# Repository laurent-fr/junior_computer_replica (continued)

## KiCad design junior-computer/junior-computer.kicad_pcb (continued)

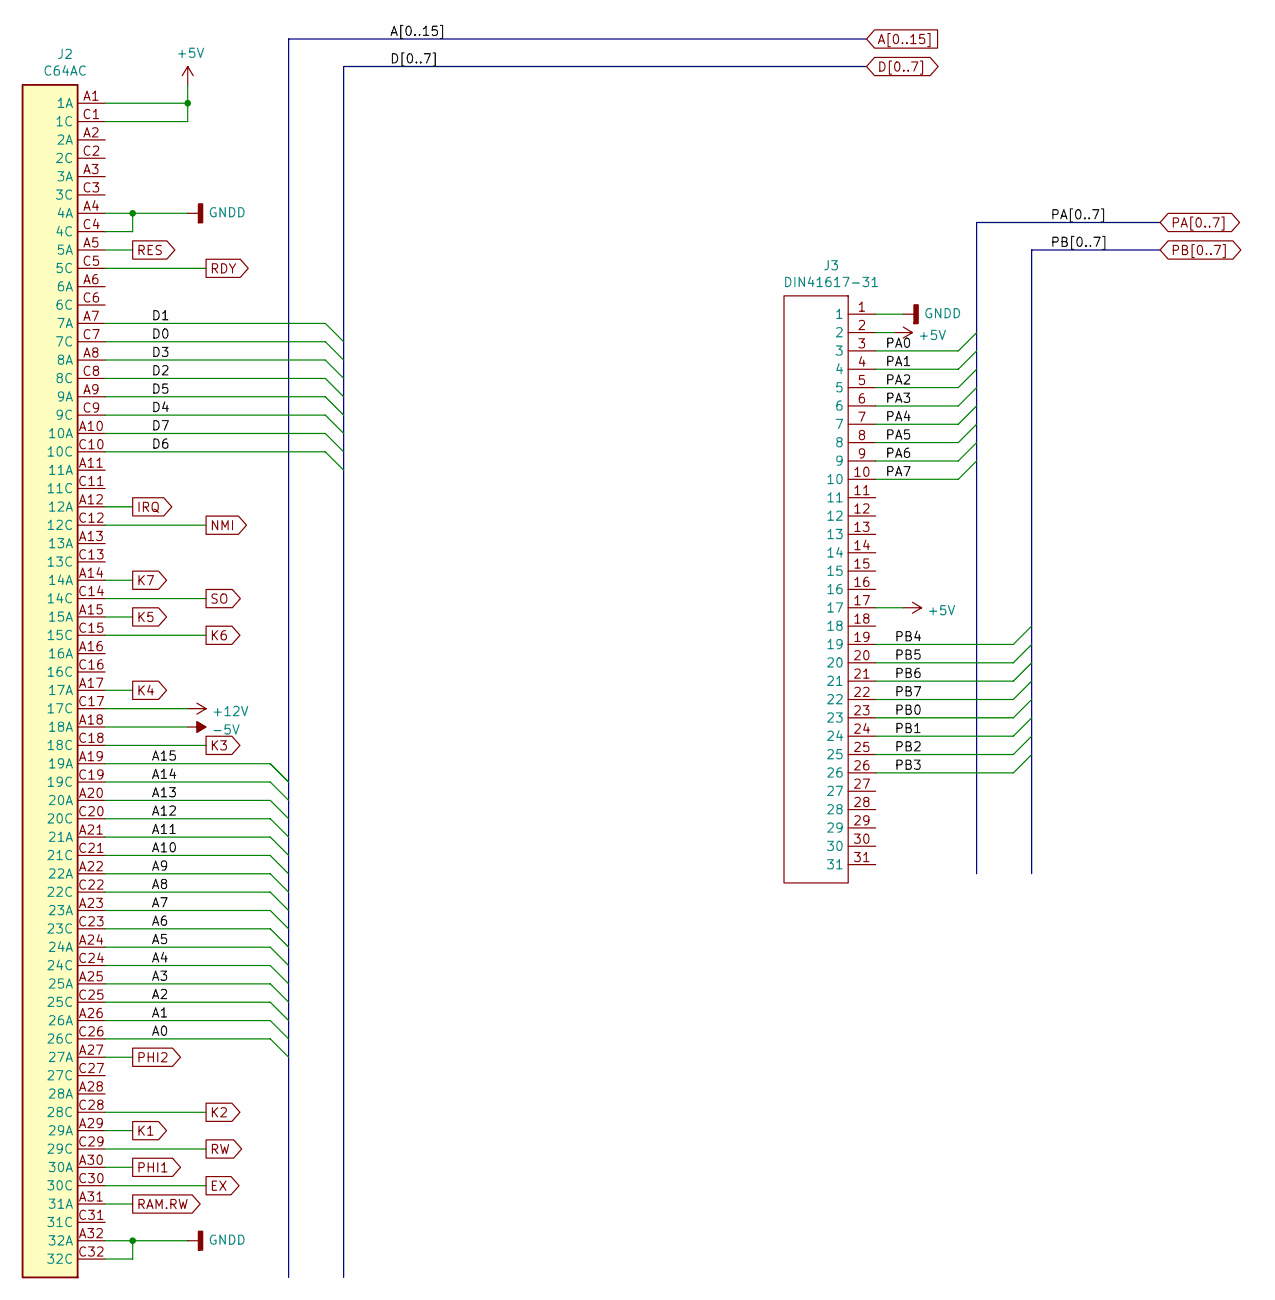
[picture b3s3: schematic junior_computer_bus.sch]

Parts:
J2: C64AC; DIN-41612-AC
J3: DIN41617-31; DIN-41617-31-F

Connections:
+5V: J2.A1 (1A), J2.C1 (1C), J3.2, J3.17; also elsewhere on the board
+12V: J2.C17 (17C)
-5V: J2.A18 (18A)
A0: J2.C26 (26C); also elsewhere on the board
A1: J2.A26 (26A); also elsewhere on the board
A2: J2.C25 (25C); also elsewhere on the board
A3: J2.A25 (25A); also elsewhere on the board
A4: J2.C24 (24C); also elsewhere on the board
A5: J2.A24 (24A); also elsewhere on the board
A6: J2.C23 (23C); also elsewhere on the board
A7: J2.A23 (23A); also elsewhere on the board
A8: J2.C22 (22C); also elsewhere on the board
A9: J2.A22 (22A); also elsewhere on the board
A10: J2.C21 (21C); also elsewhere on the board
A11: J2.A21 (21A); also elsewhere on the board
A12: J2.C20 (20C); also elsewhere on the board
A13: J2.A20 (20A); also elsewhere on the board
A14: J2.C19 (19C); also elsewhere on the board
A15: J2.A19 (19A); also elsewhere on the board
D0: J2.C7 (7C); also elsewhere on the board
D1: J2.A7 (7A); also elsewhere on the board
D2: J2.C8 (8C); also elsewhere on the board
D3: J2.A8 (8A); also elsewhere on the board
D4: J2.C9 (9C); also elsewhere on the board
D5: J2.A9 (9A); also elsewhere on the board
D6: J2.C10 (10C); also elsewhere on the board
D7: J2.A10 (10A); also elsewhere on the board
EX: J2.C30 (30C); also elsewhere on the board
GND: J2.A4 (4A), J2.A32 (32A), J2.C4 (4C), J2.C32 (32C), J3.1; also elsewhere on the board
IRQ: J2.A12 (12A); also elsewhere on the board
K1: J2.A29 (29A); also elsewhere on the board
K2: J2.C28 (28C); also elsewhere on the board
K3: J2.C18 (18C); also elsewhere on the board
K4: J2.A17 (17A); also elsewhere on the board
K5: J2.A15 (15A); also elsewhere on the board
K6: J2.C15 (15C); also elsewhere on the board
K7: J2.A14 (14A); also elsewhere on the board
NMI: J2.C12 (12C); also elsewhere on the board
PA0: J3.3; also elsewhere on the board
PA1: J3.4; also elsewhere on the board
PA2: J3.5; also elsewhere on the board
PA3: J3.6; also elsewhere on the board
PA4: J3.7; also elsewhere on the board
PA5: J3.8; also elsewhere on the board
PA6: J3.9; also elsewhere on the board
PA7: J3.10; also elsewhere on the board
PB0: J3.23; also elsewhere on the board
PB1: J3.24; also elsewhere on the board
PB2: J3.25; also elsewhere on the board
PB3: J3.26; also elsewhere on the board
PB4: J3.19; also elsewhere on the board
PB5: J3.20; also elsewhere on the board
PB6: J3.21; also elsewhere on the board
PB7: J3.22; also elsewhere on the board
PHI1: J2.A30 (30A); also elsewhere on the board
PHI2: J2.A27 (27A); also elsewhere on the board
RAM.RW: J2.A31 (31A); also elsewhere on the board
RDY: J2.C5 (5C); also elsewhere on the board
RES: J2.A5 (5A); also elsewhere on the board
RW: J2.C29 (29C); also elsewhere on the board
SO: J2.C14 (14C); also elsewhere on the board

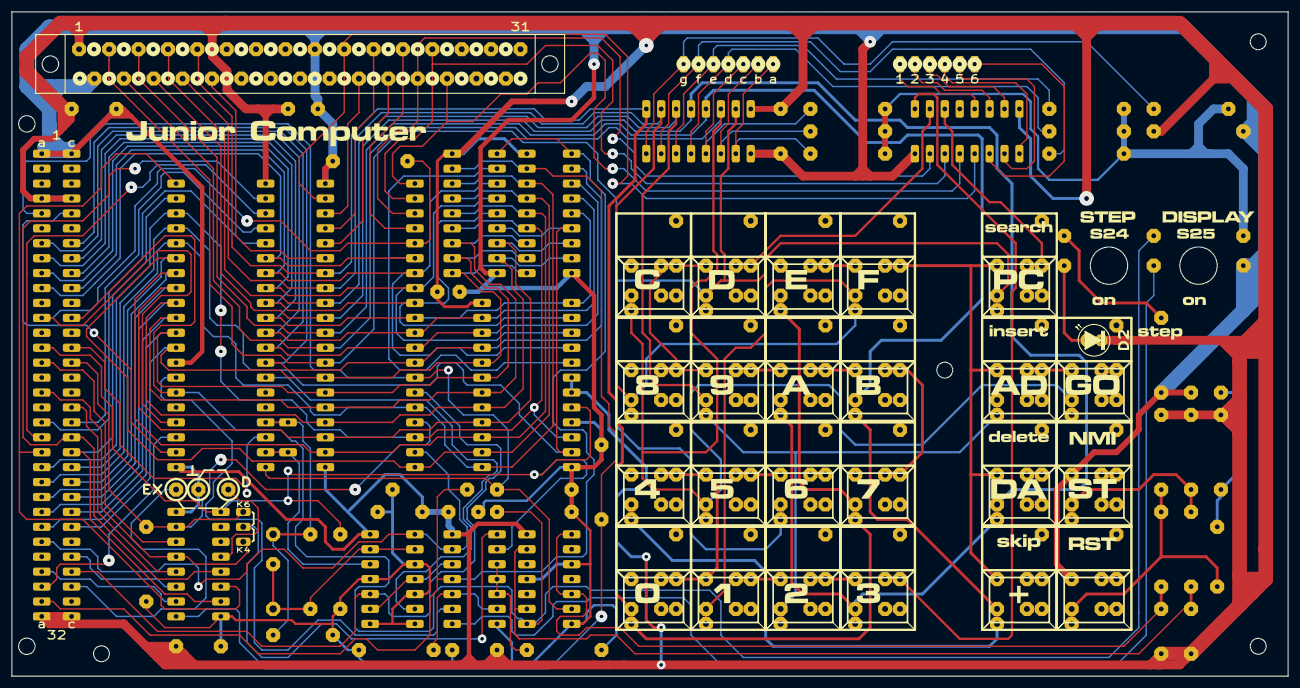
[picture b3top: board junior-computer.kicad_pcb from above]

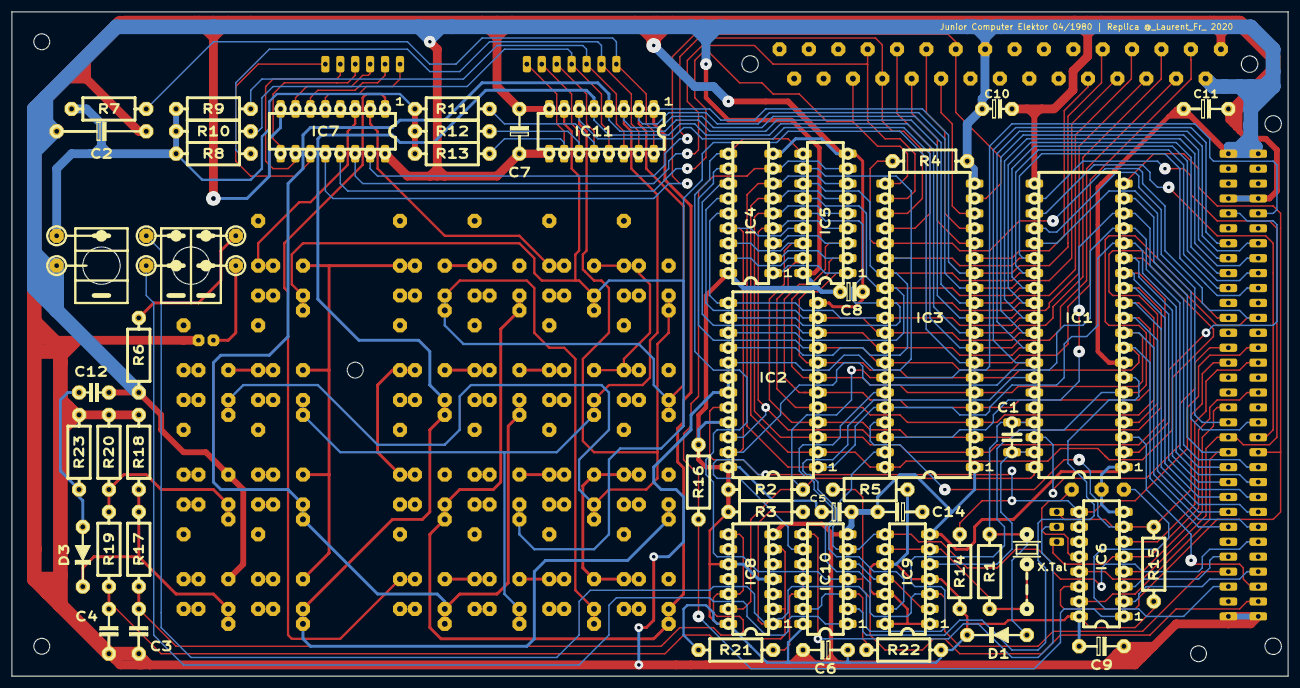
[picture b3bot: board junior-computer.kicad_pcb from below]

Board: 2 copper layers, 217.2 x 113.0 mm, 82 parts (52 on the bottom side), 95 nets.

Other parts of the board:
Ref**: Val**; lettrages2
X.Tal: 1Mhz; Quartz

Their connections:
unnamed 39: X.Tal.2; also elsewhere on the board
unnamed 65: X.Tal.1; also elsewhere on the board

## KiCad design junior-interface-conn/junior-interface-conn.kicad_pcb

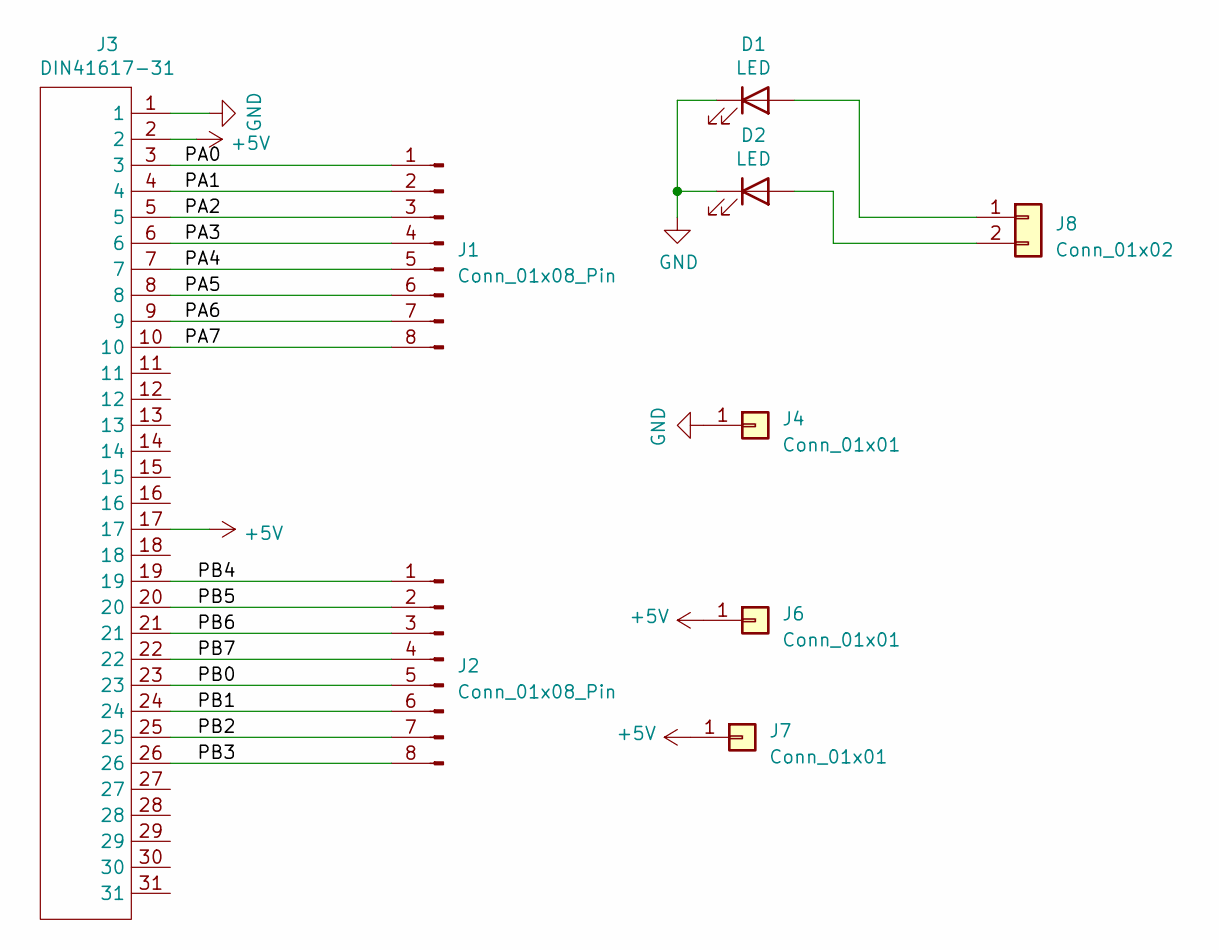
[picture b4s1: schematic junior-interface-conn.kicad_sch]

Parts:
D1, D2: LED
J1, J2: Conn_01x08_Pin; CONN-8
J3: DIN41617-31; DIN-41617-31-M
J4, J6, J7: Conn_01x01; CONN-1
J8: Conn_01x02; CONN-2-L

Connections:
+5V: J3.2, J3.17, J6.1, J7.1
/PA0: J1.1, J3.3
/PA1: J1.2, J3.4
/PA2: J1.3, J3.5
/PA3: J1.4, J3.6
/PA4: J1.5, J3.7
/PA5: J1.6, J3.8
/PA6: J1.7, J3.9
/PA7: J1.8, J3.10
/PB0: J2.5, J3.23
/PB1: J2.6, J3.24
/PB2: J2.7, J3.25
/PB3: J2.8, J3.26
/PB4: J2.1, J3.19
/PB5: J2.2, J3.20
/PB6: J2.3, J3.21
/PB7: J2.4, J3.22
GND: D1.1 (K), D2.1 (K), J3.1, J4.1
unnamed: D1.2 (A), J8.1
unnamed: D2.2 (A), J8.2

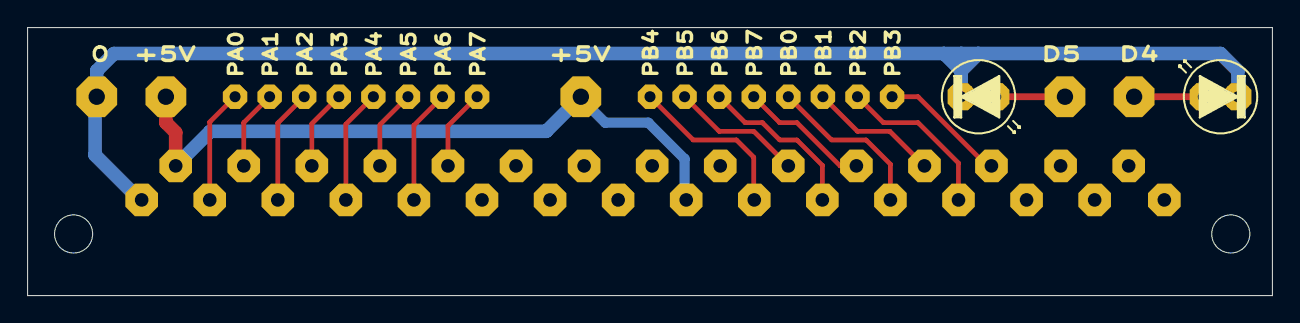
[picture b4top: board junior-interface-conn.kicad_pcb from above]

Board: 2 copper layers, 91.4 x 19.7 mm, 9 parts (1 on the bottom side), 20 nets.

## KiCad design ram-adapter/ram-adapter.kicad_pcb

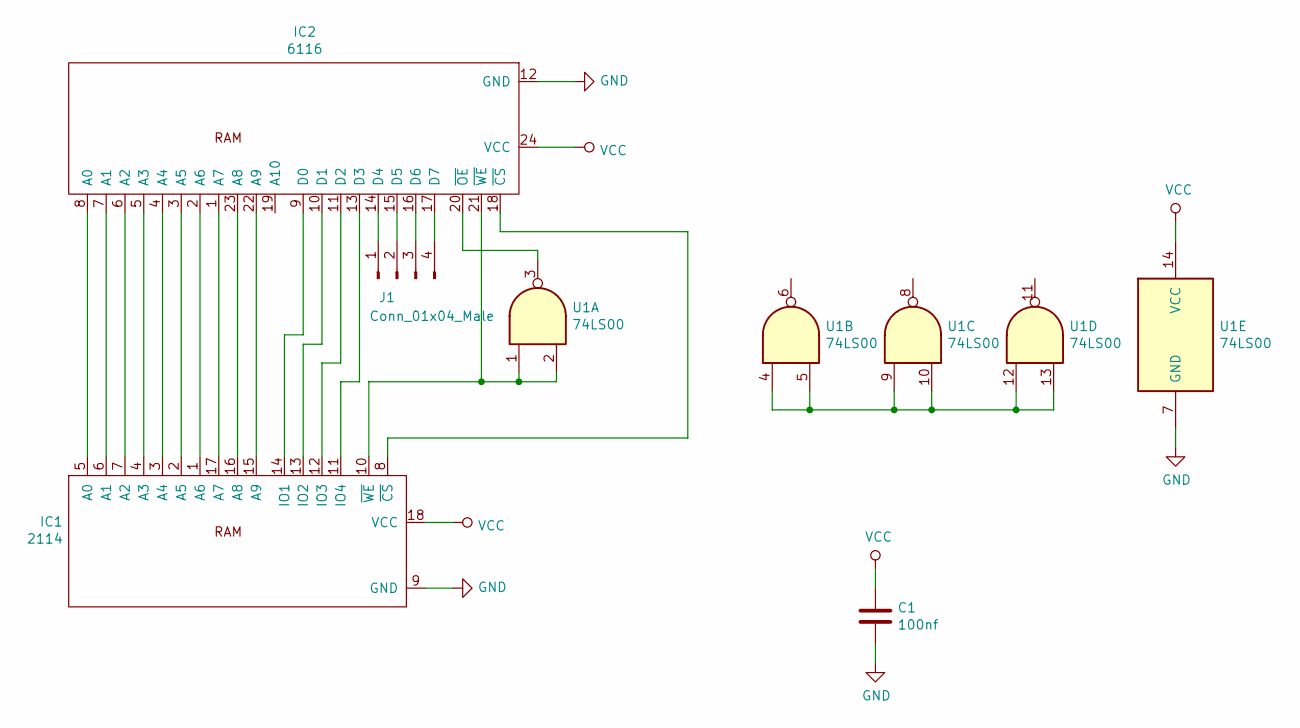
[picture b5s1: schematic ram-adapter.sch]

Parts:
C1: 100nf; C_Rect_L7.0mm_W2.0mm_P5.00mm
IC1: 2114; DIP-18_W7.62mm
IC2: 6116; DIP-24_W15.24mm
J1: Conn_01x04_Male; Pin_Header_Straight_1x04_Pitch2.54mm
U1: 74LS00; DIP-14_W7.62mm

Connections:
GND: C1.2, IC1.9 (GND), IC2.12 (GND), U1.7 (GND)
unnamed: IC1.1 (A6), IC2.2 (A6)
unnamed: IC1.2 (A5), IC2.3 (A5)
unnamed: IC1.3 (A4), IC2.4 (A4)
unnamed: IC1.4 (A3), IC2.5 (A3)
unnamed: IC1.5 (A0), IC2.8 (A0)
unnamed: IC1.6 (A1), IC2.7 (A1)
unnamed: IC1.7 (A2), IC2.6 (A2)
unnamed: IC1.8 (~CS~), IC2.18 (~CS~)
unnamed: IC1.10 (~WE~), IC2.21 (~WE~), U1.1, U1.2
unnamed: IC1.11 (IO4), IC2.13 (D3)
unnamed: IC1.12 (IO3), IC2.11 (D2)
unnamed: IC1.13 (IO2), IC2.10 (D1)
unnamed: IC1.14 (IO1), IC2.9 (D0)
unnamed: IC1.15 (A9), IC2.22 (A9)
unnamed: IC1.16 (A8), IC2.23 (A8)
unnamed: IC1.17 (A7), IC2.1 (A7)
unnamed: IC2.14 (D4), J1.1
unnamed: IC2.15 (D5), J1.2
unnamed: IC2.16 (D6), J1.3
unnamed: IC2.17 (D7), J1.4
unnamed: IC2.20 (~OE~), U1.3
unnamed: U1.4, U1.5, U1.9, U1.10, U1.12, U1.13
VCC: C1.1, IC1.18 (VCC), IC2.24 (VCC), U1.14 (VCC)

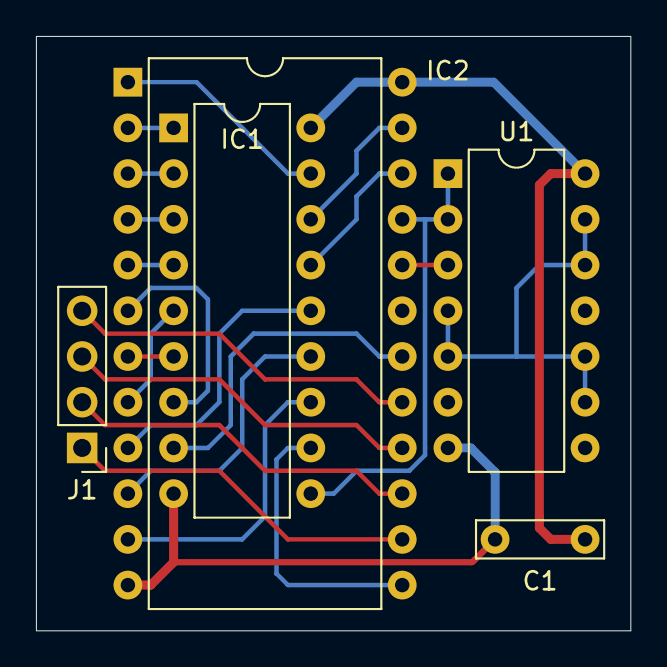
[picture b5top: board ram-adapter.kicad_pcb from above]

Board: 2 copper layers, 33.0 x 33.0 mm, 5 parts (0 on the bottom side), 24 nets.

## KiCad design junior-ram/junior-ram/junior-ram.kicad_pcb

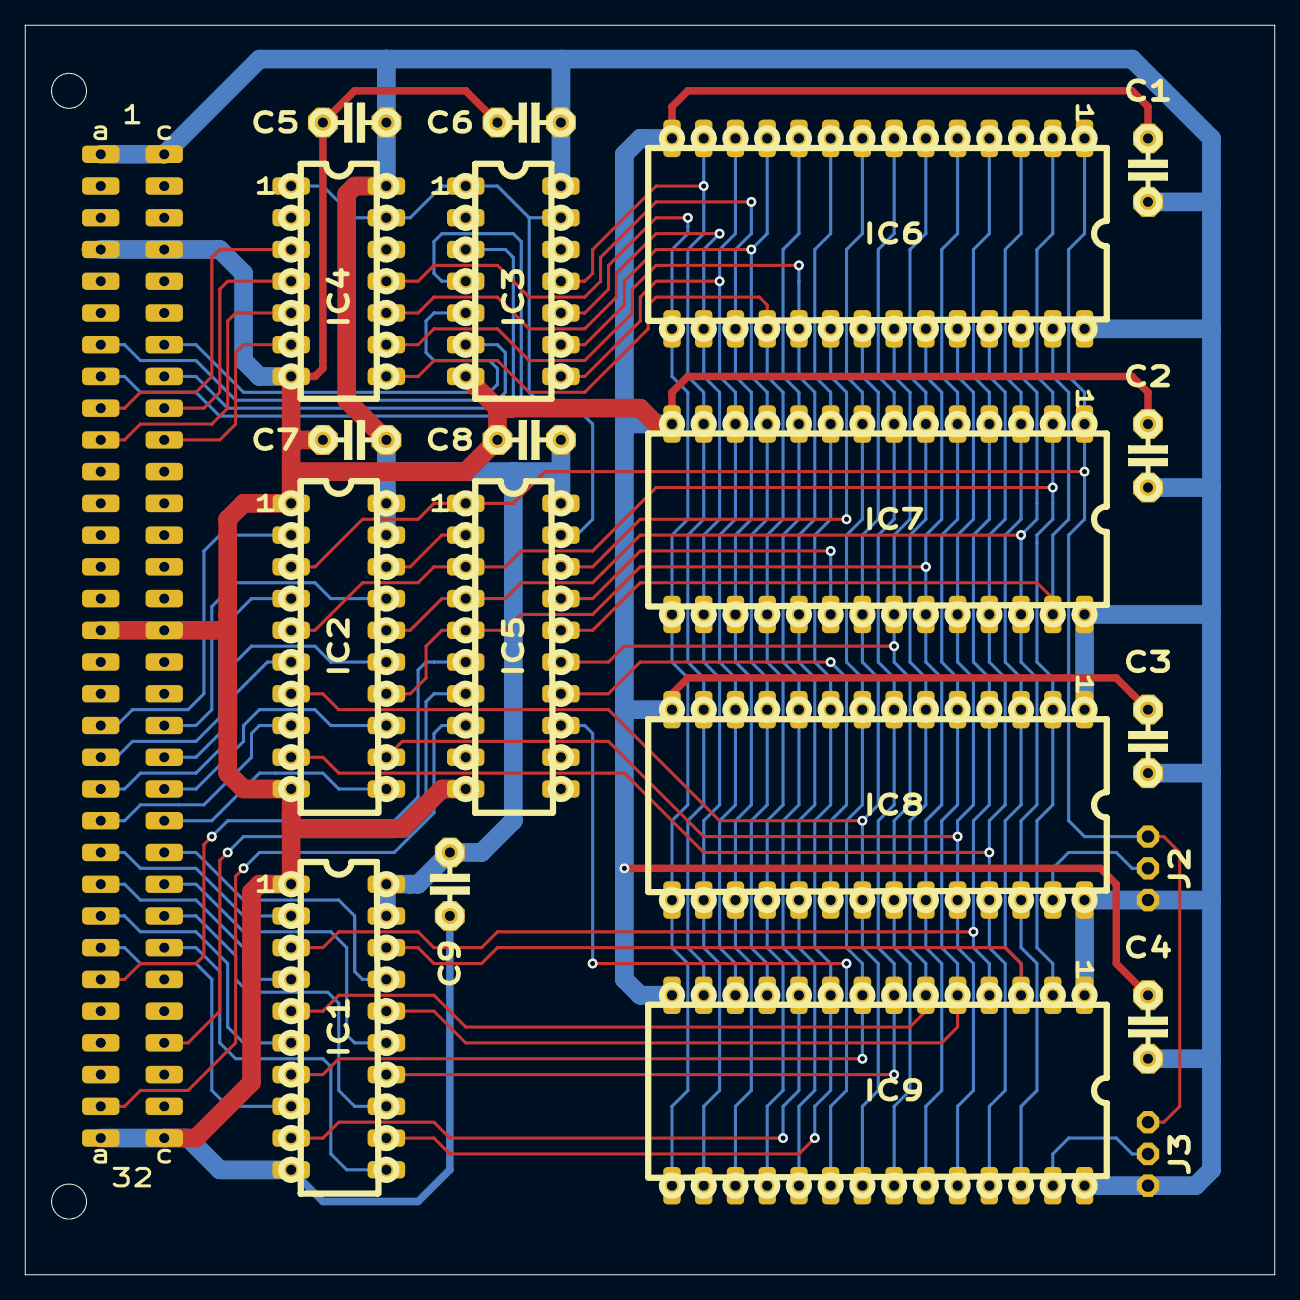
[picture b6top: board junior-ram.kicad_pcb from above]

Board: 2 copper layers, 100.0 x 100.0 mm, 21 parts (0 on the bottom side), 62 nets.

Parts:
C1, C2, C3, C4, C5, C6, C7, C8, C9: 100n; CAP-2-HEX
IC1, IC2: 74LS241; DIL-20
IC3, IC4: 74LS243; DIL-14
IC5: GAL16V8; DIL-20
IC6, IC7: 62256; DIL-28
IC8, IC9: 27C256; DIL-28
J1: C64AC; DIN-41612-AC
J2, J3: Conn_01x03_Male; CONN-3

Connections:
+5V: C1.1, C2.1, C3.1, C4.1, C5.1, C6.1, C7.1, C8.1, C9.1, IC1.19, IC1.20, IC2.19, IC2.20, IC3.14, IC4.14, IC5.20, IC6.28, IC7.28, IC8.1, IC8.28, IC9.1, IC9.28, J1.A1, J1.C1, J2.3, J3.3
A0: IC1.11, J1.C26
A1: IC1.8, J1.A26
A2: IC1.13, J1.C25
A3: IC1.6, J1.A25
A4: IC1.15, J1.C24
A5: IC1.4, J1.A24
A6: IC1.17, J1.C23
A7: IC1.2, J1.A23
A8: IC2.11, J1.C22
A9: IC2.8, J1.A22
A10: IC2.13, J1.C21
A11: IC2.6, J1.A21
A12: IC2.15, J1.C20
A13: IC2.4, J1.A20
A14: IC2.17, J1.C19
A15: IC2.2, J1.A19
AB0: IC1.9, IC6.10, IC7.10, IC8.10, IC9.10
AB1: IC1.12, IC6.9, IC7.9, IC8.9, IC9.9
AB2: IC1.7, IC6.8, IC7.8, IC8.8, IC9.8
AB3: IC1.14, IC6.7, IC7.7, IC8.7, IC9.7
AB4: IC1.5, IC6.6, IC7.6, IC8.6, IC9.6
AB5: IC1.16, IC6.5, IC7.5, IC8.5, IC9.5
AB6: IC1.3, IC6.4, IC7.4, IC8.4, IC9.4
AB7: IC1.18, IC6.3, IC7.3, IC8.3, IC9.3
AB8: IC2.9, IC6.25, IC7.25, IC8.25, IC9.25
AB9: IC2.12, IC6.24, IC7.24, IC8.24, IC9.24
AB10: IC2.7, IC6.21, IC7.21, IC8.21, IC9.21
AB11: IC2.14, IC5.5, IC6.23, IC7.23, IC8.23, IC9.23
AB12: IC2.5, IC5.3, IC6.2, IC7.2, IC8.2, IC9.2
AB13: IC2.16, IC5.4, IC6.26, IC7.26, IC8.26, IC9.26
AB14: IC2.3, IC5.1, IC6.1, IC7.1, J2.1, J3.1
AB15: IC2.18, IC5.2
D0: IC3.5, J1.C7
D1: IC3.6, J1.A7
D2: IC3.3, J1.C8
D3: IC3.4, J1.A8
D4: IC4.4, J1.C9
D5: IC4.3, J1.A9
D6: IC4.6, J1.C10
D7: IC4.5, J1.A10
D.DIR: IC3.1, IC3.13, IC4.1, IC4.13, IC5.19
DB0: IC3.9, IC6.11, IC7.11, IC8.11, IC9.11
DB1: IC3.8, IC6.12, IC7.12, IC8.12, IC9.12
DB2: IC3.11, IC6.13, IC7.13, IC8.13, IC9.13
DB3: IC3.10, IC6.15, IC7.15, IC8.15, IC9.15
DB4: IC4.10, IC6.16, IC7.16, IC8.16, IC9.16
DB5: IC4.11, IC6.17, IC7.17, IC8.17, IC9.17
DB6: IC4.8, IC6.18, IC7.18, IC8.18, IC9.18
DB7: IC4.9, IC6.19, IC7.19, IC8.19, IC9.19
GND: C1.2, C2.2, C3.2, C4.2, C5.2, C6.2, C7.2, C8.2, C9.2, IC1.1, IC1.10, IC2.1, IC2.10, IC3.7, IC4.7, IC5.10, IC6.14, IC7.14, IC8.14, IC9.14, J1.A4, J1.A16, J1.A32, J1.C4, J1.C16, J1.C32
unnamed: IC8.27, J2.2
unnamed: IC9.27, J3.2
OE: IC5.15, IC6.22, IC7.22, IC8.22, IC9.22
PHI2: IC5.6, J1.A27
RAM.CS1: IC5.18, IC6.20
RAM.CS2: IC5.17, IC7.20
RAM.RW: IC5.8, J1.A31
ROM.CS1: IC5.14, IC8.20
ROM.CS2: IC5.13, IC9.20
RW: IC5.7, J1.C29
WE: IC5.16, IC6.27, IC7.27

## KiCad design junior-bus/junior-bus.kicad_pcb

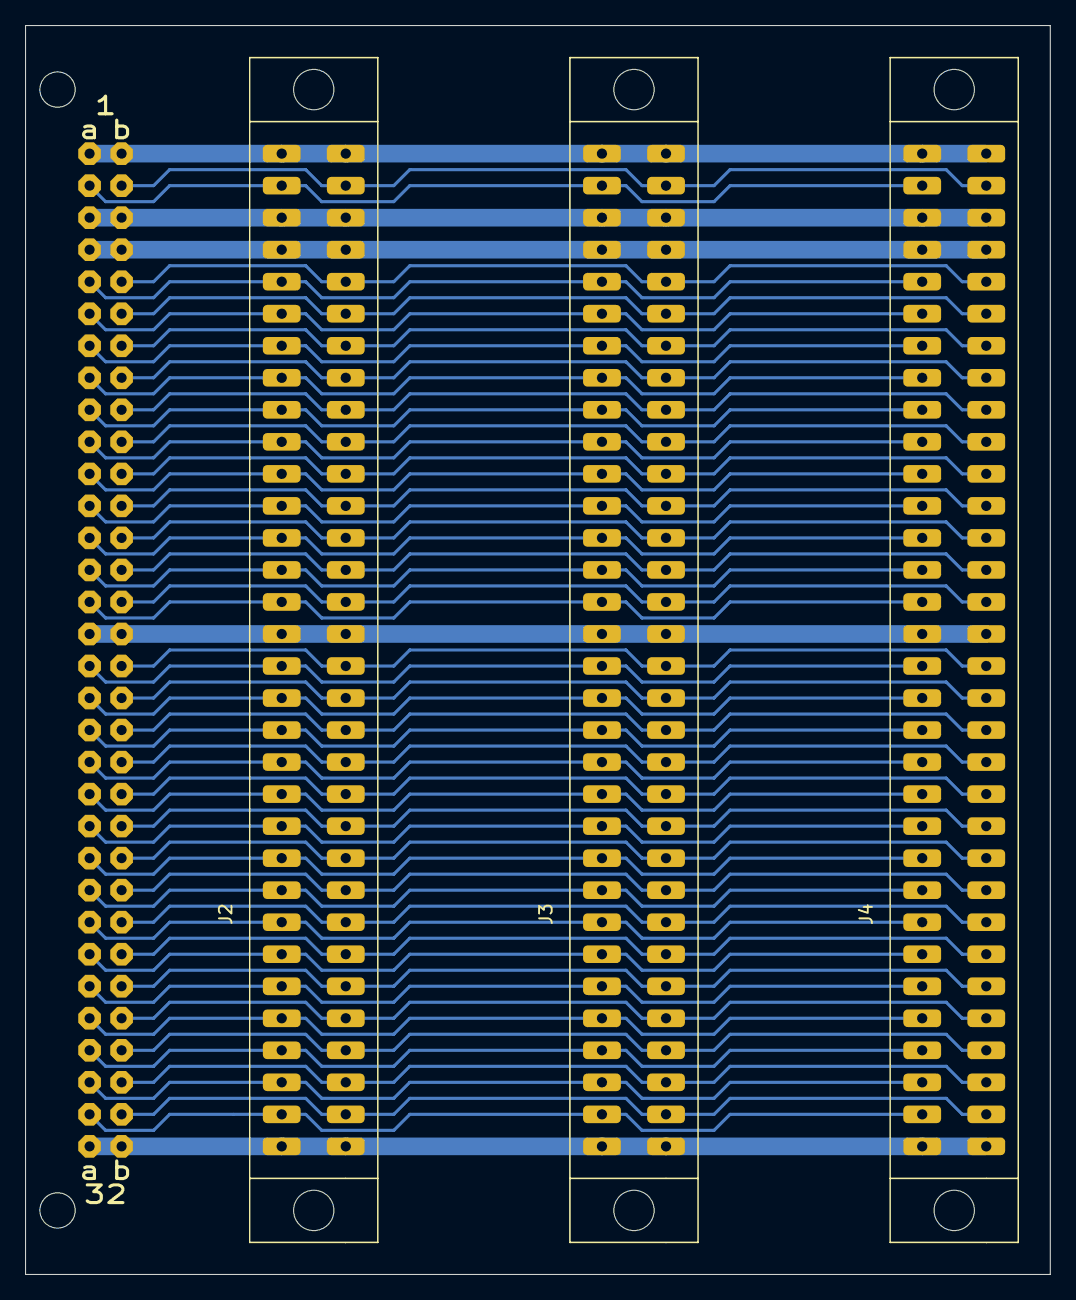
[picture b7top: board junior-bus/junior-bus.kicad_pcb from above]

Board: 2 copper layers, 81.3 x 99.1 mm, 4 parts (0 on the bottom side), 57 nets.

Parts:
J1: C64AB; DIN-41612-AB
J2, J3, J4: C64AC; DI41612-AC-F

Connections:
2A: J1.A2, J2.A2, J3.A2, J4.A2
2C: J1.B2, J2.C2, J3.C2, J4.C2
6A: J1.A6, J2.A6, J3.A6, J4.A6
6C: J1.B6, J2.C6, J3.C6, J4.C6
11A: J1.A11, J2.A11, J3.A11, J4.A11
11C: J1.B11, J2.C11, J3.C11, J4.C11
13A: J1.A13, J2.A13, J3.A13, J4.A13
13C: J1.B13, J2.C13, J3.C13, J4.C13
14A: J1.A14, J2.A14, J3.A14, J4.A14
15A: J1.A15, J2.A15, J3.A15, J4.A15
17A: J1.A17, J2.A17, J3.A17, J4.A17
18C: J1.B18, J2.C18, J3.C18, J4.C18
27A: J1.A27, J2.A27, J3.A27, J4.A27
27C: J1.B27, J2.C27, J3.C27, J4.C27
28A: J1.A28, J2.A28, J3.A28, J4.A28
28C: J1.B28, J2.C28, J3.C28, J4.C28
29A: J1.A29, J2.A29, J3.A29, J4.A29
31C: J1.B31, J2.C31, J3.C31, J4.C31
+5V: J1.A1, J1.B1, J2.A1, J2.C1, J3.A1, J3.C1, J4.A1, J4.C1
+12V: J1.B17, J2.C17, J3.C17, J4.C17
-5V: J1.A18, J2.A18, J3.A18, J4.A18
-12V: J1.A3, J1.B3, J2.A3, J2.C3, J3.A3, J3.C3, J4.A3, J4.C3
/A0: J1.B26, J2.C26, J3.C26, J4.C26
/A1: J1.A26, J2.A26, J3.A26, J4.A26
/A2: J1.B25, J2.C25, J3.C25, J4.C25
/A3: J1.A25, J2.A25, J3.A25, J4.A25
/A4: J1.B24, J2.C24, J3.C24, J4.C24
/A5: J1.A24, J2.A24, J3.A24, J4.A24
/A6: J1.B23, J2.C23, J3.C23, J4.C23
/A7: J1.A23, J2.A23, J3.A23, J4.A23
/A8: J1.B22, J2.C22, J3.C22, J4.C22
/A9: J1.A22, J2.A22, J3.A22, J4.A22
/A10: J1.B21, J2.C21, J3.C21, J4.C21
/A11: J1.A21, J2.A21, J3.A21, J4.A21
/A12: J1.B20, J2.C20, J3.C20, J4.C20
/A13: J1.A20, J2.A20, J3.A20, J4.A20
/A14: J1.B19, J2.C19, J3.C19, J4.C19
/A15: J1.A19, J2.A19, J3.A19, J4.A19
/D0: J1.B7, J2.C7, J3.C7, J4.C7
/D1: J1.A7, J2.A7, J3.A7, J4.A7
/D2: J1.B8, J2.C8, J3.C8, J4.C8
/D3: J1.A8, J2.A8, J3.A8, J4.A8
/D4: J1.B9, J2.C9, J3.C9, J4.C9
/D5: J1.A9, J2.A9, J3.A9, J4.A9
/D6: J1.B10, J2.C10, J3.C10, J4.C10
/D7: J1.A10, J2.A10, J3.A10, J4.A10
C15: J1.B15, J2.C15, J3.C15, J4.C15
EX: J1.B30, J2.C30, J3.C30, J4.C30
GND: J1.A4, J1.A16, J1.A32, J1.B4, J1.B16, J1.B32, J2.A4, J2.A16, J2.A32, J2.C4, J2.C16, J2.C32, J3.A4, J3.A16, J3.A32, J3.C4, J3.C16, J3.C32, J4.A4, J4.A16, J4.A32, J4.C4, J4.C16, J4.C32
IRQ: J1.A12, J2.A12, J3.A12, J4.A12
NMI: J1.B12, J2.C12, J3.C12, J4.C12
PHI1: J1.A30, J2.A30, J3.A30, J4.A30
RAM.RW: J1.A31, J2.A31, J3.A31, J4.A31
RDY: J1.B5, J2.C5, J3.C5, J4.C5
RES: J1.A5, J2.A5, J3.A5, J4.A5
RW: J1.B29, J2.C29, J3.C29, J4.C29
SO: J1.B14, J2.C14, J3.C14, J4.C14

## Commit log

2020-10-02 'routing'
2020-10-03 routage complet
2020-10-03 amelioration dessin pistes
2020-10-04 lettrage
2020-10-07 modifs schema
2020-10-08 correction empreintes
2020-10-09 correction stencil
2020-10-10 finition platine
2020-10-10 ram adapter
2020-10-11 version commandée
2020-10-24 junior interface
2020-10-25 junior interface schema
2020-10-25 junior interface routage
2020-10-31 junior interface routage complet
2020-10-31 junior interface modifs
2020-11-03 junior bus
2020-11-04 junior ram
2020-11-05 junior ram routage complet
2022-07-23 README update
2022-07-23 add license file
2022-07-23 adding monitor ROM
2022-07-23 add pictures
2022-07-23 Add images
2022-07-23 Correct twitter link
2024-10-19 fix R1 value, add C9
2024-12-01 junior interface update
2024-12-01 fix README
2024-12-01 correct image name
2024-12-08 update Junior Bus subproject
2024-12-08 fix - correct central M3.2 hole position
2024-12-08 fix - bad DIN41612 footprint, bad distance between connectors
2024-12-08 add junior-universal-memory subproject / remove junior-ram subproject
2024-12-21 update status of bus&memory boards
2024-12-21 add REAdME
2024-12-21 Update README.md
    fix tables
2024-12-21 going further section
2024-12-21 fix typos
2024-12-21 add memory board picture
2024-12-21 typo
